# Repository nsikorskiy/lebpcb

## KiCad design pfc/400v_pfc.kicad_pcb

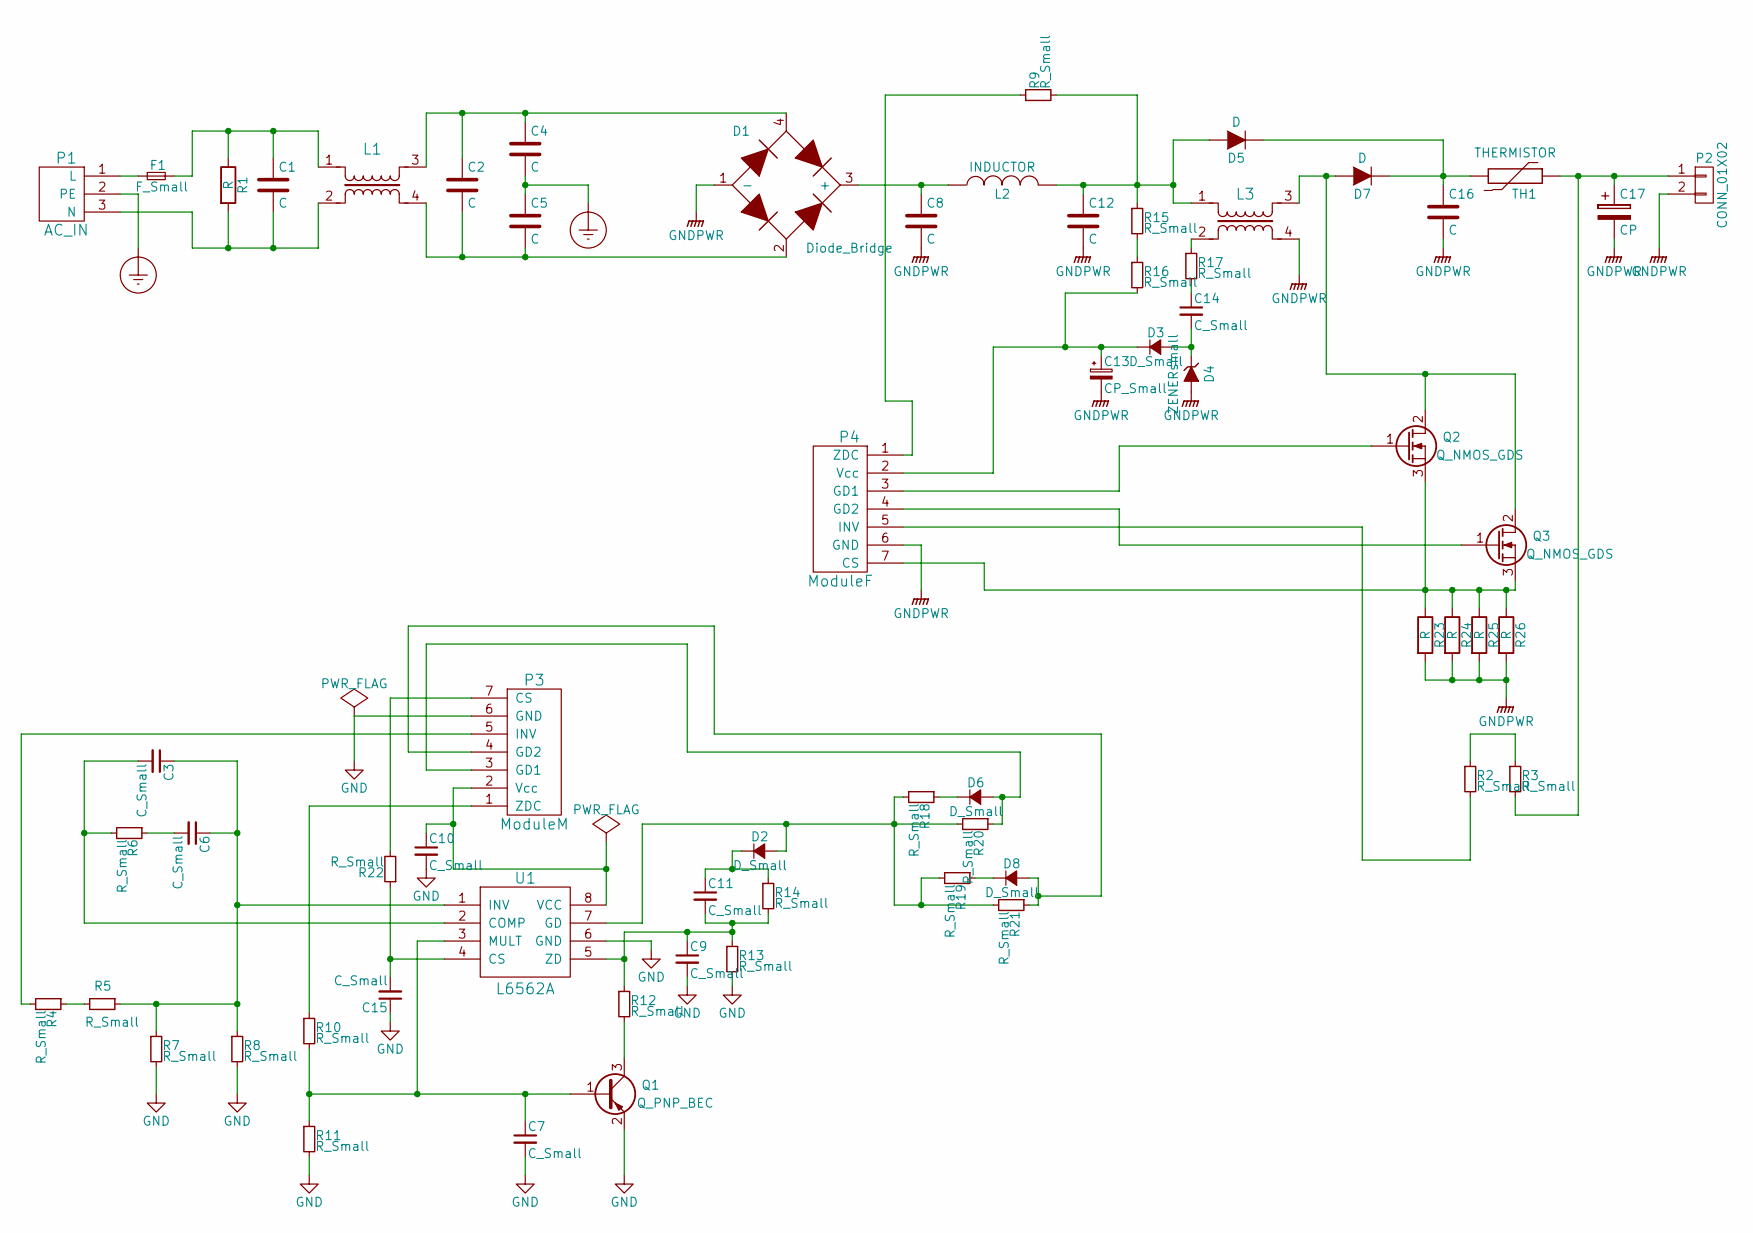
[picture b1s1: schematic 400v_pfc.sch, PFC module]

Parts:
C1, C2: C; C_Rect_L13_W4_P10
C3, C9, C11, C15: C_Small; C_0805
C4, C5: C; C_Rect_L18_W5_P15
C6, C7, C10, C14: C_Small; C_1206
C8, C12, C16: C; C_Rect_L18_W6_H12_P15
C13: CP_Small; C_Radial_D8_L11.5_P3.5
C17: CP; C_Radial_D35_L51_P10
D1: Diode_Bridge; diode_bridge
D2, D3, D6, D8: D_Small; MiniMELF_Standard
D4: ZENERsmall; MiniMELF_Standard
D5: D; Diode_DO-201AD_Horizontal_RM15
D7: D; Diode_TO-220_Vertical
F1: F_Small; Fuseholder5x20_horiz_open_lateral_Type-II
L1, L3: emp_filter
L2: INDUCTOR; INDUCTOR_V
P1: AC_IN; bornier3
P2: CONN_01X02; bornier2
P3: ModuleM
P4: ModuleF; ModuleX
Q1: Q_PNP_BEC; SOT-23
Q2, Q3: Q_NMOS_GDS; TO-220_Neutral123_Vertical_LargePads
R1, R23, R24, R25, R26: R; Resistor_Horizontal_RM15mm
R2, R3, R4, R5, R9, R10, R11, R15, R16, R17, R22: R_Small; R_1206
R6, R7, R8, R12, R13, R14, R18, R19, R20, R21: R_Small; R_0805
TH1: THERMISTOR; Resistor_Horizontal_RM10mm
U1: L6562A; SO-8

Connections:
Earth_Protective: C4.2, C5.1, P1.2 (PE)
GND: C7.2, C9.2, C10.2, C15.1, P3.6 (GND), Q1.2 (E), R7.2, R8.2, R11.2, R13.2, U1.6 (GND)
GNDPWR: C8.2, C12.2, C13.2, C16.2, C17.2, D1.1 (-), D4.2 (A), L3.4, P2.2, P4.6 (GND), R23.2, R24.2, R25.2, R26.2
unnamed: C1.1, F1.2, L1.1, R1.1
unnamed: C1.2, L1.2, P1.3 (N), R1.2
unnamed: C2.1, C4.1, D1.4, L1.3
unnamed: C2.2, C5.2, D1.2, L1.4
unnamed: C3.1, C6.1, R5.1, R7.1, R8.1, U1.1 (INV)
unnamed: C3.2, R6.2, U1.2 (COMP)
unnamed: C6.2, R6.1
unnamed: C7.1, Q1.1 (B), R10.2, R11.1, U1.3 (MULT)
unnamed: C8.1, D1.3 (+), L2.1
unnamed: C10.1, P3.2 (Vcc), U1.8 (VCC)
unnamed: C11.1, D2.1 (K), R14.1
unnamed: C9.1, C11.2, R12.1, R13.1, R14.2, U1.5 (ZD)
unnamed: C12.1, D5.2 (A), L2.2, L3.1, R9.2, R15.1
unnamed: C13.1, D3.1 (K), P4.2 (Vcc), R16.2
unnamed: C14.1, R17.2
unnamed: C14.2, D3.2 (A), D4.1 (K)
unnamed: C15.2, R22.1, U1.4 (CS)
unnamed: C16.1, D5.1 (K), D7.1 (K), TH1.2
unnamed: C17.1, P2.1, R3.2, TH1.1
unnamed: D2.2 (A), R18.2, R19.2, R20.2, R21.2, U1.7 (GD)
unnamed: D6.1 (K), R18.1
unnamed: D6.2 (A), P3.3 (GD1), R20.1
unnamed: D7.2 (A), L3.3, Q2.2 (D), Q3.2 (D)
unnamed: D8.1 (K), R19.1
unnamed: D8.2 (A), P3.4 (GD2), R21.1
unnamed: F1.1, P1.1 (L)
unnamed: L3.2, R17.1
unnamed: P3.1 (ZDC), R10.1
unnamed: P3.5 (INV), R4.2
unnamed: P3.7 (CS), R22.2
unnamed: P4.1 (ZDC), R9.1
unnamed: P4.3 (GD1), Q2.1 (G)
unnamed: P4.4 (GD2), Q3.1 (G)
unnamed: P4.5 (INV), R2.2
unnamed: P4.7 (CS), Q2.3 (S), Q3.3 (S), R23.1, R24.1, R25.1, R26.1
unnamed: Q1.3 (C), R12.2
unnamed: R2.1, R3.1
unnamed: R4.1, R5.2
unnamed: R15.2, R16.1

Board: 2 copper layers, 64 parts (36 on the bottom side), 42 nets, no tracks yet.

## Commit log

2016-09-23 init add
